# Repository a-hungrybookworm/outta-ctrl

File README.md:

# Outta-Ctrl

A custom 64-key tactile mechanical keyboard designed from scratch - including a custom PCB, case, firmware, and even keycaps. 

## Features
* Custom PCB & layout
* 3D designed sandwich-mount case
* Custom RMK firmware
* Tactile MX-compatible switches
* Screw-in stabilisers
* Custom keycaps

## Components 
* Custom PCB
* 3D-printed case
* Tactile Gateron switches
* 1N4148 diodes
* Raspberry Pi Pico 
* Clear screw-in stabilizers
* Blank white (soon-to-be-doodled-on) keycaps

## Design Process
Initially, I planned the 64-key layout for my keyboard, and decided which components I would use. 

I then designed the PCB in KiCAD. I initially figured out which libraries/ footprints to use, connected them to form the keyboard matrix (row-to-col) and finally arranged the components and routed the traces.

Next, I learnt how to 3D model in Onshape, while simultaneously modelling the [case](https://cad.onshape.com/documents/6f7a7e00666188f7ad4cf98b/w/f1435142402e02a68e5f24dd/e/d5e9a1b6849998dde5a38184). I used a sandwich mount for its simplicity, but ended up removing the top (above the plate) to cut costs, and split the case as it was too big for the bed size. 

Finally, I wrote the RMK firmware, which I will flash to my Pi Pico to control the keyboard.

## Why I built it
I've been fascinated by understanding how most everyday objects work, and when I saw a HackClub programme offering to teach me how to build one of them, a keyboard, I was thrilled. Finally, I had the opportunity to learn how to design keyboard PCBs, model their cases, write their custom firmware, and deeply understand how these devices function.

## Challenges
While designing the keyboard, I found several tasks challenging, such as
* understanding the specifications and limitations of the different components
* accounting for all the specific holes and features of the components while designing the 3D models
* finding footprints/ 3D models for my components
* finding keycaps for my design size

## What I learnt
I started this ambitious project with no experience at all, and only a list of tutorials (credit to [Keeb](keeb.hackclub.com)). Now, I've learnt so much, including (sequentially) - 
* how Github repositories function 
* how to write in Markdown, and how to write a readme
* how to design a PCB in KiCAD
* the matrix layout/schematic required for keyboard PCBs
* how to use Onshape for 3D designing
* the different keyboard mounting styles, and parts of a case
* what keyboard firmware does, and how to write it
* about different keyboard components, and their functions

## Images 

__Schematic__:

__Routed PCB__: 

**3D Models:**

 __Plate__:

 __Base__:

__Assembly__:

(without all keycaps/ stabs)

# Bill of Materials (BOM)

| SI No. | Name | Notes | Quantity | Price / Unit (INR) | Shipping (INR) | Total (INR) | Running Total (INR) | Price/Unit (USD) | Total (USD) | Running Total (USD) | Link | Vendor |
| --- | --- | --- | --- | ---: | ---: | ---: | ---: | ---: | ---: | ---: | --- | --- |
| 1 | Gateron G Pro 3.0 Brown Tactile Switches (Pack of 10) | MX-compatible Switches | 7 | 190 | 0 | 1330 | 1330 | 2.02 | 14.15 | 14.15 | [Switch](https://stackskb.com/store/gateron-g-pro-3-0-brown-ks-9-tactile-switch-pack-of-10/) | StacksKB |
| 2 | PCB (manufactured by Robu) | Manufactured by Robu | 5 | 1066.60 | 0 | 5333 | 6663 | 11.35 | 56.73 | 70.88 | [PCB_Robu](https://github.com/a-hungrybookworm/outta-ctrl/blob/main/BOM/PCB_Quote.png) | Robu |
| 3 | Durock Clear Screw-In Stabilizers V2 | Screw-in stabilisers | 1 | 1650 | 0 | 1650 | 8313 | 17.55 | 17.55 | 88.44 | [Stabs](https://stackskb.com/store/durock-clear-screw-in-stabilizers-v2/) | StacksKB |
| 4 | 1N4148 Diodes | Keyboard matrix | 65 | 1.07 | 49 | 118.55 | 8431.55 | 0.01 | 1.26 | 89.70 | [Diodes](https://robu.in/product/1n4148-1w-zener-diode-pack-of-50/) | Robu |
| 5 | Raspberry Pi Pico | MCU | 1 | 422 | 0 | 422 | 8853.55 | 4.49 | 4.49 | 94.19 | [Pico](https://robu.in/product/raspberry-pi-pico/) | Robu |
| 6 | Brass Threaded Inserts | M3x6mm | 8 | 2.80 | 0 | 22.40 | 8875.95 | 0.03 | 0.24 | 94.43 | [Heat Set Insert](https://onlyscrews.in/products/m3-x-6mm-brass-threaded-inserts?variant=49418769203513) | OnlyScrews |
| 7 | M3 X 10mm Phillips Pan head Screw | M3x10mm, shipping includes taxes | 8 | 0.66 | 73.98 | 79.26 | 8955.21 | 0.01 | 0.84 | 95.27 | [Screws](https://onlyscrews.in/products/m3-x-10mm-phillips-pan-head-mild-steel-with-zinc-blue-plating-screw-dia-3mm-length-10mm?variant=52636241887545) | OnlyScrews |
| 8 | Blank White Cherry Profile Keycaps | For later customization | 1 | 1000 | 0 | 1000 | 9955.21 | 10.64 | 10.64 | 105.91 | [Keycaps](https://stackskb.com/store/stackspbt-blank-white-cherry-profile-keycaps-113-key/) | StacksKB |
| 9 | 7u Spacebar | Custom key | 1 | 300 | 0 | 300 | 10255.21 | 3.19 | 3.19 | 109.10 | [Spacebar](https://curiositycaps.in/products/7u-spacebar-replacement-key) | CuriosityCaps |
| 10 | 3D Print | Case! | 1 | 1333.86 | 100 | 1433.86 | 11689.07 | 14.19 | 15.25 | 124.35 | [3DP_Quote](https://github.com/a-hungrybookworm/outta-ctrl/blob/main/BOM/3D_Printing_Quote.png) | Printing Legion |
|  | **Total (with shipping)** |  |  |  |  |  | **11689.07** |  |  | **124.35** |  |  |

**Exchange rate used:** ₹94 ≈ $1  
**Grand total:** ₹11,689.07 / **$124.35**

## Credits
This project was made possible through open-source hardware and design resources, and continuous support from the mechanical keyboard community. A special thank-you to the Hackclub YSWS Keeb, for inspiring me to take up this project, guiding me along the way, and most importantly, funding this project.

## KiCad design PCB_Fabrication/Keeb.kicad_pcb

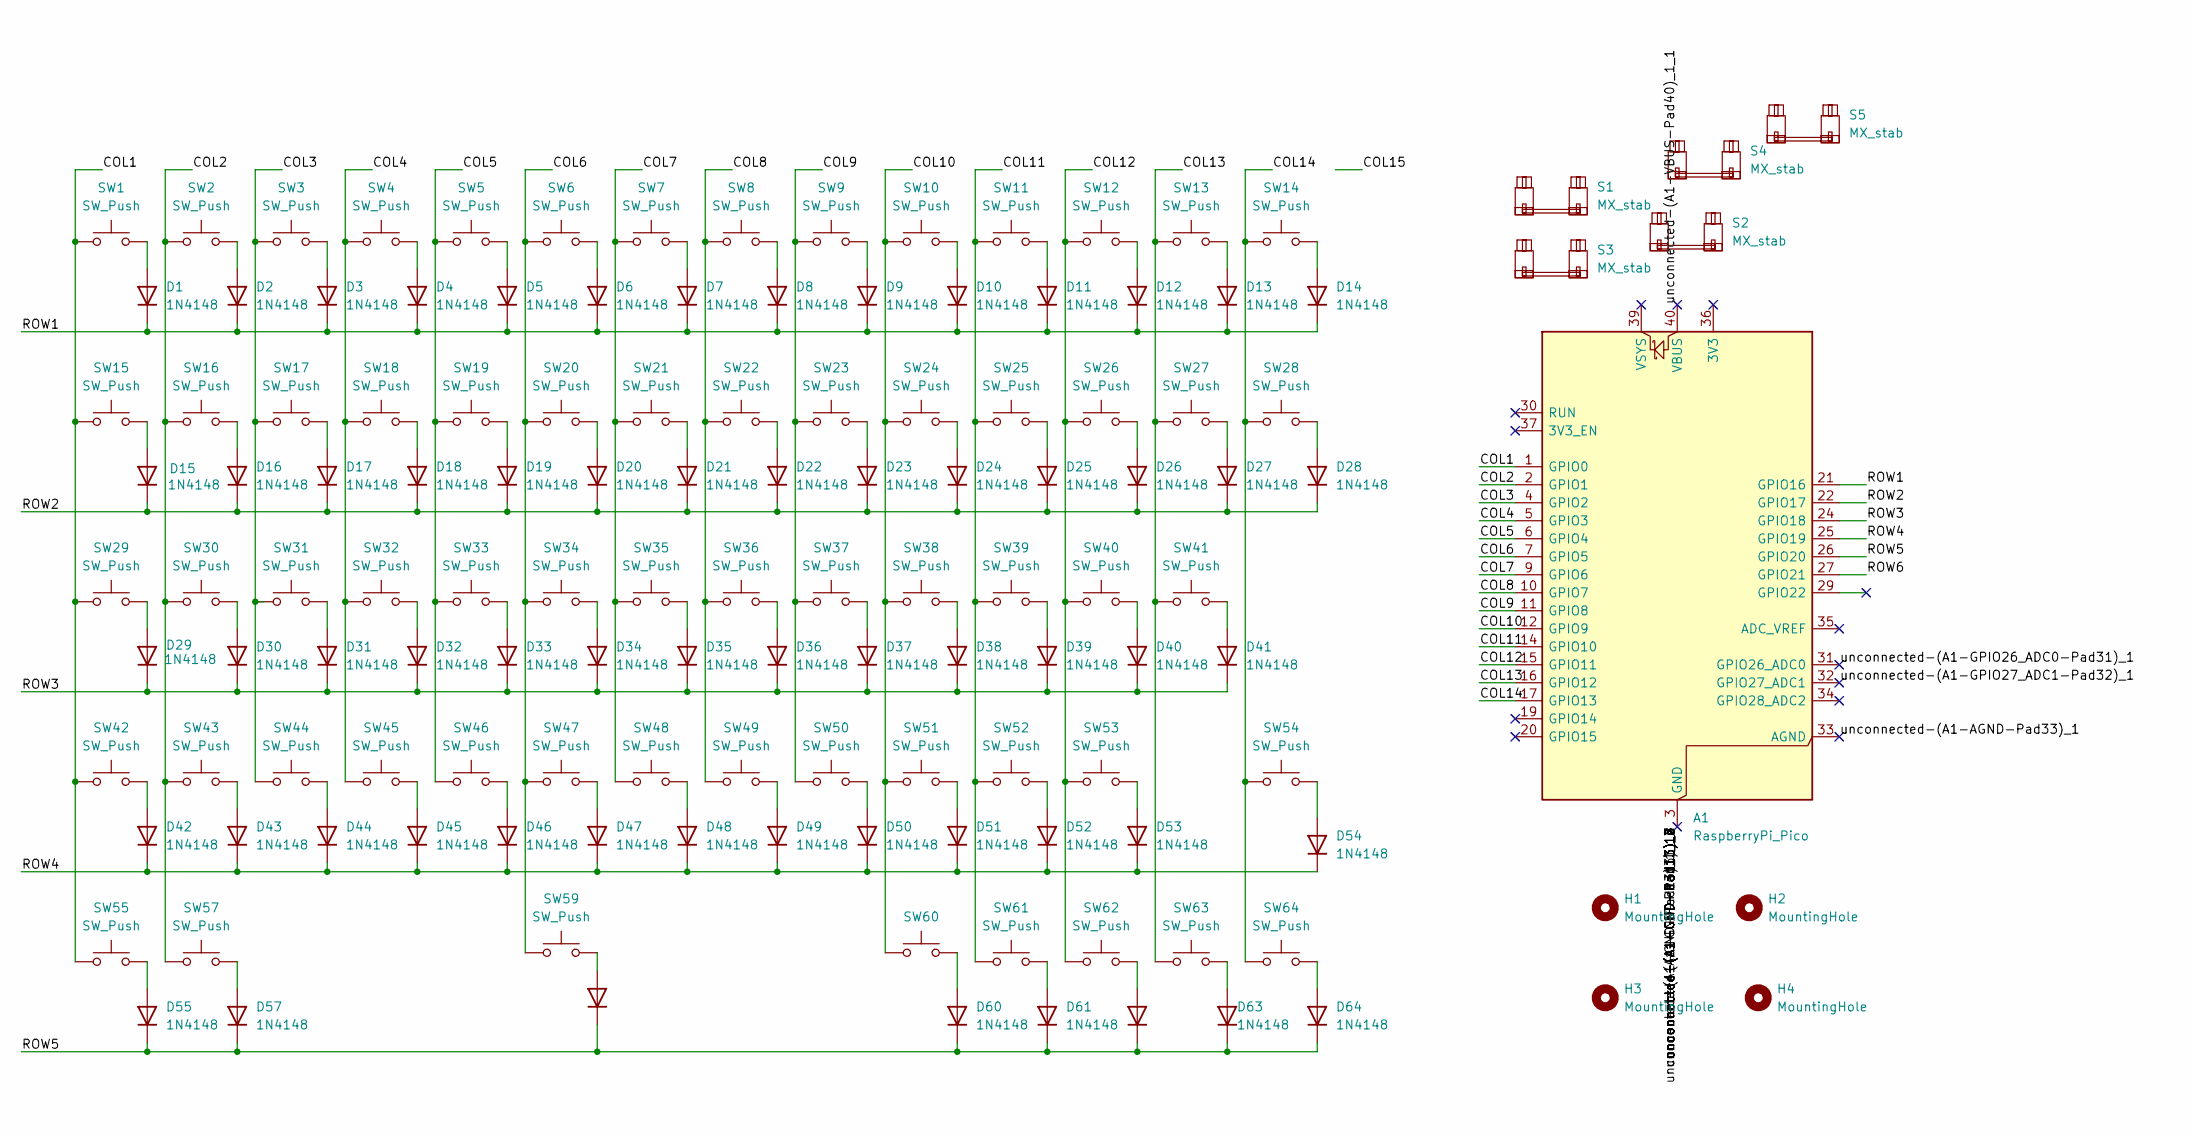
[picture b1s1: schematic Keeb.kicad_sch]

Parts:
A1: RaspberryPi_Pico; RaspberryPi_Pico_Common_Unspecified
D1, D2, D3, D4, D5, D6, D7, D8, D9, D10, D11, D12, D13, D14, D15, D16, D17, D18, D19, D20, D21, D22, D23, D24, D25, D26, D27, D28, D29, D30, D31, D32, D33, D34, D35, D36, D37, D38, D39, D40, D41, D42, D43, D44, D45, D46, D47, D48, D49, D50, D51, D52, D53, D54, D55, D57, D59, D60, D61, D62, D63, D64: 1N4148; D_DO-35_SOD27_P7.62mm_Horizontal
H1, H2, H3, H4: MountingHole; MountingHole_4.3mm_M4
S1, S3, S4, S5: MX_stab; STAB_MX_2u
S2: MX_stab; STAB_MX_7u
SW1, SW2, SW3, SW4, SW5, SW6, SW7, SW8, SW9, SW10, SW11, SW12, SW13, SW14, SW15, SW16, SW17, SW18, SW19, SW20, SW21, SW22, SW23, SW24, SW25, SW26, SW27, SW28, SW29, SW30, SW31, SW32, SW33, SW34, SW35, SW36, SW37, SW38, SW39, SW40, SW41, SW42, SW43, SW44, SW45, SW46, SW47, SW48, SW49, SW50, SW51, SW52, SW53, SW54, SW55, SW57, SW59, SW60, SW61, SW62, SW63, SW64: SW_Push; SW_MX_1u

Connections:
/COL1: A1.1 (GPIO0), SW1.1, SW15.1, SW29.1, SW42.1, SW55.1
/COL2: A1.2 (GPIO1), SW2.1, SW16.1, SW30.1, SW43.1, SW57.1
/COL3: A1.4 (GPIO2), SW3.1, SW17.1, SW31.1, SW44.1
/COL4: A1.5 (GPIO3), SW4.1, SW18.1, SW32.1, SW45.1
/COL5: A1.6 (GPIO4), SW5.1, SW19.1, SW33.1, SW46.1
/COL6: A1.7 (GPIO5), SW6.1, SW20.1, SW34.1, SW47.1, SW59.1
/COL7: A1.9 (GPIO6), SW7.1, SW21.1, SW35.1, SW48.1
/COL8: A1.10 (GPIO7), SW8.1, SW22.1, SW36.1, SW49.1
/COL9: A1.11 (GPIO8), SW9.1, SW23.1, SW37.1, SW50.1
/COL10: A1.12 (GPIO9), SW10.1, SW24.1, SW38.1, SW51.1, SW60.1
/COL11: A1.14 (GPIO10), SW11.1, SW25.1, SW39.1, SW52.1, SW61.1
/COL12: A1.15 (GPIO11), SW12.1, SW26.1, SW40.1, SW53.1, SW62.1
/COL13: A1.16 (GPIO12), SW13.1, SW27.1, SW41.1, SW63.1
/COL14: A1.17 (GPIO13), SW14.1, SW28.1, SW54.1, SW64.1
/ROW1: A1.21 (GPIO16), D1.1 (K), D2.1 (K), D3.1 (K), D4.1 (K), D5.1 (K), D6.1 (K), D7.1 (K), D8.1 (K), D9.1 (K), D10.1 (K), D11.1 (K), D12.1 (K), D13.1 (K), D14.1 (K)
/ROW2: A1.22 (GPIO17), D15.1 (K), D16.1 (K), D17.1 (K), D18.1 (K), D19.1 (K), D20.1 (K), D21.1 (K), D22.1 (K), D23.1 (K), D24.1 (K), D25.1 (K), D26.1 (K), D27.1 (K), D28.1 (K)
/ROW3: A1.24 (GPIO18), D29.1 (K), D30.1 (K), D31.1 (K), D32.1 (K), D33.1 (K), D34.1 (K), D35.1 (K), D36.1 (K), D37.1 (K), D38.1 (K), D39.1 (K), D40.1 (K), D41.1 (K)
/ROW4: A1.25 (GPIO19), D42.1 (K), D43.1 (K), D44.1 (K), D45.1 (K), D46.1 (K), D47.1 (K), D48.1 (K), D49.1 (K), D50.1 (K), D51.1 (K), D52.1 (K), D53.1 (K), D54.1 (K)
/ROW5: A1.26 (GPIO20), D55.1 (K), D57.1 (K), D59.1 (K), D60.1 (K), D61.1 (K), D62.1 (K), D63.1 (K), D64.1 (K)
/ROW6: A1.27 (GPIO21)
/unconnected-(A1-AGND-Pad33)_1: A1.33 (AGND)
/unconnected-(A1-AGND-Pad33)_1_1: A1.33 (AGND)
/unconnected-(A1-GND-Pad13)_12_2: A1.3 (GND)
/unconnected-(A1-GND-Pad13)_12_5: A1.23 (GND)
/unconnected-(A1-GND-Pad13)_12_8: A1.18 (GND)
/unconnected-(A1-GND-Pad13)_12_9: A1.28 (GND)
/unconnected-(A1-GND-Pad13)_12_10: A1.13 (GND)
/unconnected-(A1-GND-Pad13)_12_11: A1.8 (GND)
/unconnected-(A1-GND-Pad13)_12_13: A1.38 (GND)
/unconnected-(A1-GPIO26_ADC0-Pad31)_1: A1.31 (GPIO26_ADC0)
/unconnected-(A1-GPIO26_ADC0-Pad31)_1_1: A1.31 (GPIO26_ADC0)
/unconnected-(A1-GPIO27_ADC1-Pad32)_1: A1.32 (GPIO27_ADC1)
/unconnected-(A1-GPIO27_ADC1-Pad32)_1_1: A1.32 (GPIO27_ADC1)
/unconnected-(A1-VBUS-Pad40)_1_1: A1.40 (VBUS)
/unconnected-(A1-VBUS-Pad40)_1_1_1: A1.40 (VBUS)
unnamed: D1.2 (A), SW1.2
unnamed: D2.2 (A), SW2.2
unnamed: D3.2 (A), SW3.2
unnamed: D4.2 (A), SW4.2
unnamed: D5.2 (A), SW5.2
unnamed: D6.2 (A), SW6.2
unnamed: D7.2 (A), SW7.2
unnamed: D8.2 (A), SW8.2
unnamed: D9.2 (A), SW9.2
unnamed: D10.2 (A), SW10.2
unnamed: D11.2 (A), SW11.2
unnamed: D12.2 (A), SW12.2
unnamed: D13.2 (A), SW13.2
unnamed: D14.2 (A), SW14.2
unnamed: D15.2 (A), SW15.2
unnamed: D16.2 (A), SW16.2
unnamed: D17.2 (A), SW17.2
unnamed: D18.2 (A), SW18.2
unnamed: D19.2 (A), SW19.2
unnamed: D20.2 (A), SW20.2
unnamed: D21.2 (A), SW21.2
unnamed: D22.2 (A), SW22.2
unnamed: D23.2 (A), SW23.2
unnamed: D24.2 (A), SW24.2
unnamed: D25.2 (A), SW25.2
unnamed: D26.2 (A), SW26.2
unnamed: D27.2 (A), SW27.2
unnamed: D28.2 (A), SW28.2
unnamed: D29.2 (A), SW29.2
unnamed: D30.2 (A), SW30.2
unnamed: D31.2 (A), SW31.2
unnamed: D32.2 (A), SW32.2
unnamed: D33.2 (A), SW33.2
unnamed: D34.2 (A), SW34.2
unnamed: D35.2 (A), SW35.2
unnamed: D36.2 (A), SW36.2
unnamed: D37.2 (A), SW37.2
unnamed: D38.2 (A), SW38.2
unnamed: D39.2 (A), SW39.2
unnamed: D40.2 (A), SW40.2
unnamed: D41.2 (A), SW41.2
unnamed: D42.2 (A), SW42.2
unnamed: D43.2 (A), SW43.2
unnamed: D44.2 (A), SW44.2
unnamed: D45.2 (A), SW45.2
unnamed: D46.2 (A), SW46.2
unnamed: D47.2 (A), SW47.2
unnamed: D48.2 (A), SW48.2
unnamed: D49.2 (A), SW49.2
unnamed: D50.2 (A), SW50.2
unnamed: D51.2 (A), SW51.2
unnamed: D52.2 (A), SW52.2
unnamed: D53.2 (A), SW53.2
unnamed: D54.2 (A), SW54.2
unnamed: D55.2 (A), SW55.2
unnamed: D57.2 (A), SW57.2
unnamed: D59.2 (A), SW59.2
unnamed: D60.2 (A), SW60.2
unnamed: D61.2 (A), SW61.2
unnamed: D62.2 (A), SW62.2
unnamed: D63.2 (A), SW63.2
unnamed: D64.2 (A), SW64.2

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
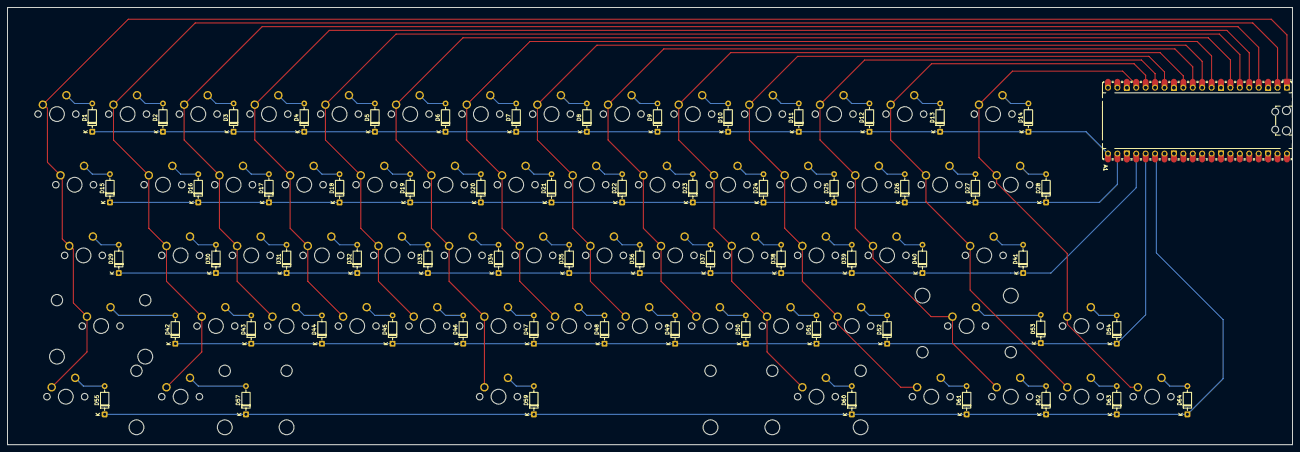
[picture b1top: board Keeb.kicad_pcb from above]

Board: 2 copper layers, 346.5 x 117.9 mm, 130 parts (0 on the bottom side), 81 nets.
